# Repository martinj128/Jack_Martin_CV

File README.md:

# Jack_Martin_CV Repo

This repositry contains some personal projects I have invested my timein and also the complete work for my Final Year Dissertation which achieved publication in the CEAS Journal "SpaceWire in a Power Over Ethernet Environment".

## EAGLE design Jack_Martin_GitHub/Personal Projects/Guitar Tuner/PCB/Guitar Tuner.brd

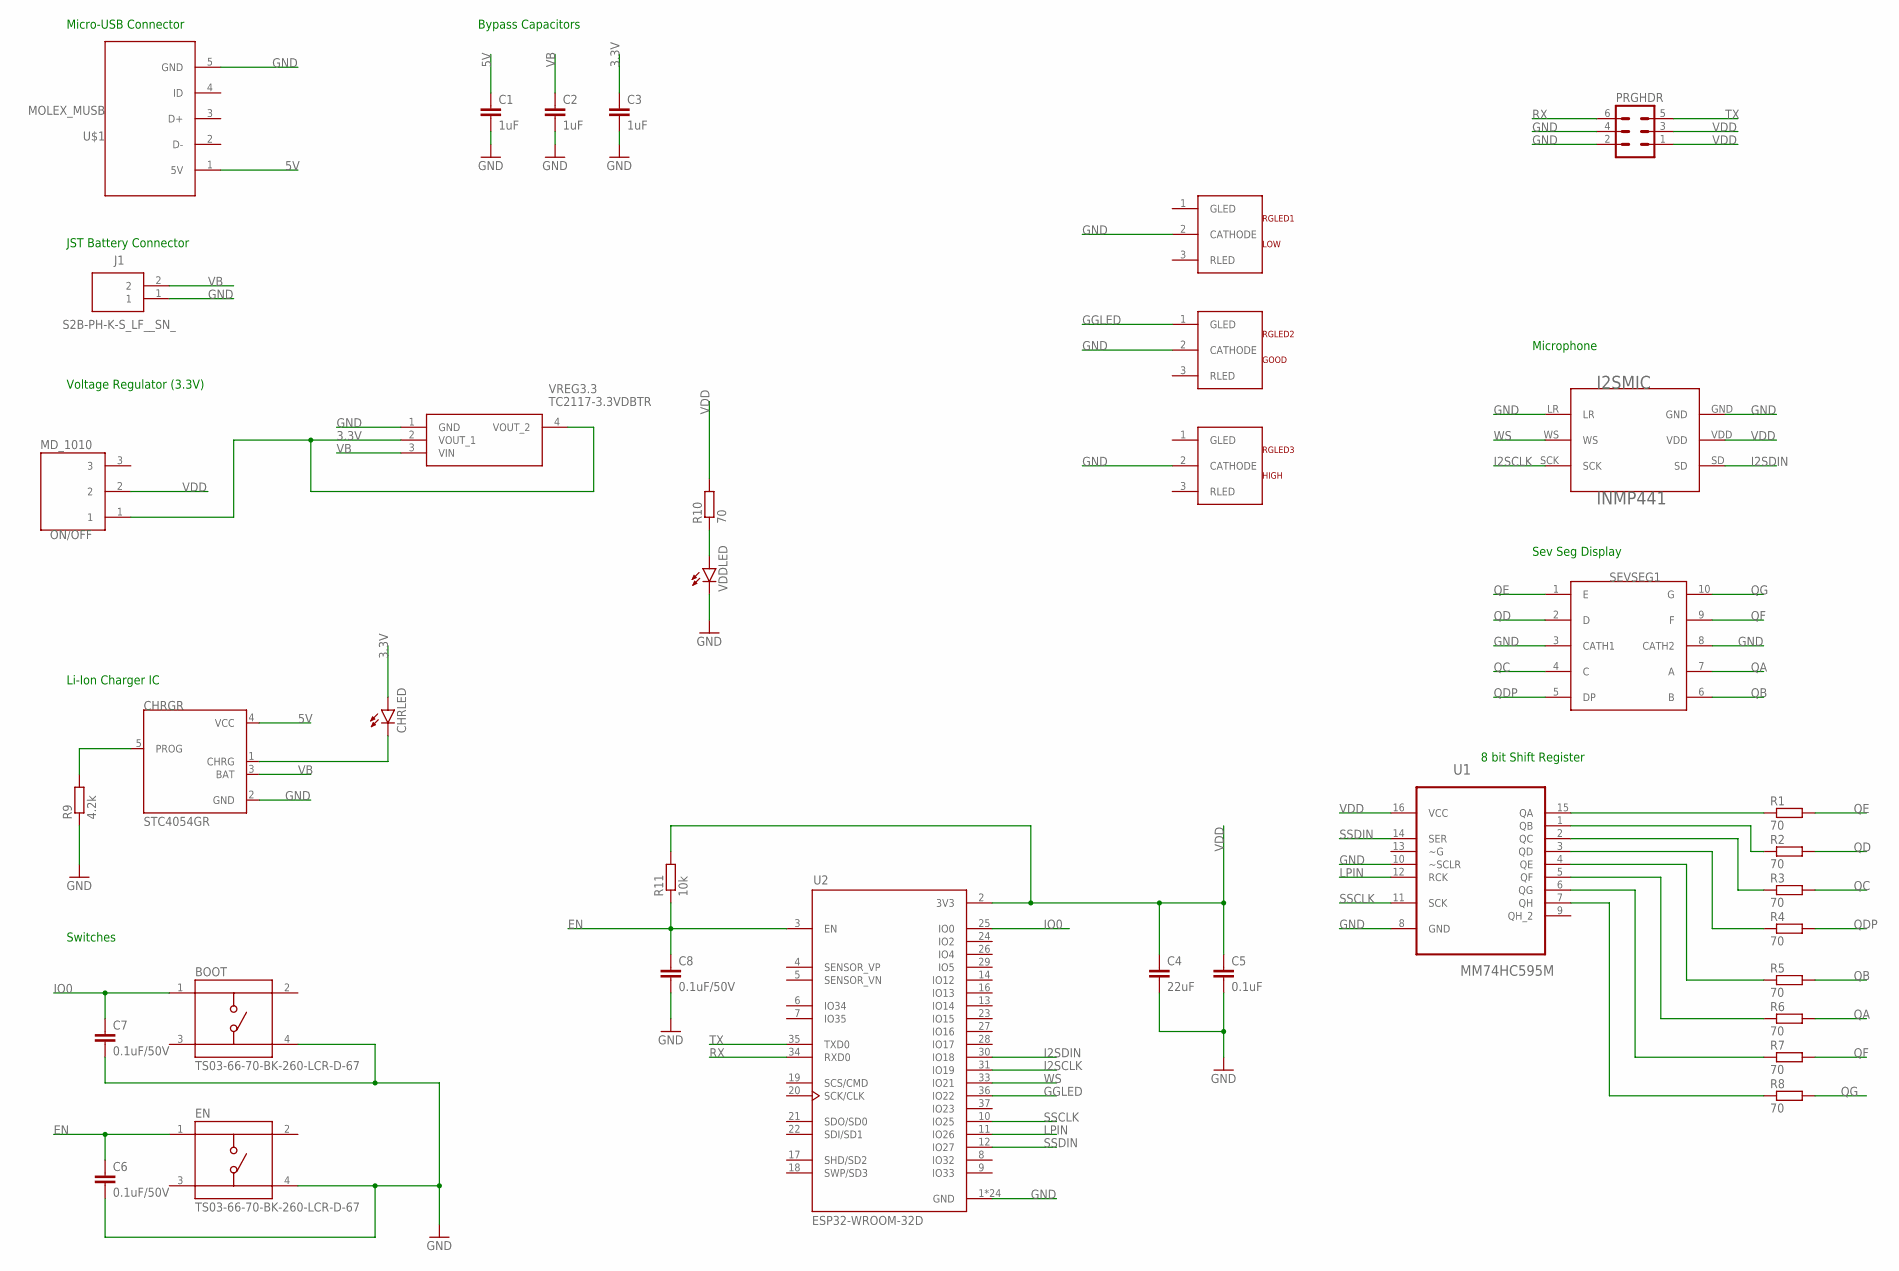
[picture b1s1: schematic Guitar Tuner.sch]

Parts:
BOOT: TS03-66-70-BK-260-LCR-D-67; SW_TS03-66-70-BK-260-LCR-D-67
C1, C2, C3: 1uF; C0805
C4: 22uF; C0805
C5: 0.1uF; C0805
C6, C7, C8: 0.1uF/50V; C0805
CHRGR: STC4054GR; SOT95P280X110-5N
CHRLED: LED5MM
EN: TS03-66-70-BK-260-LCR-D-67; SW_TS03-66-70-BK-260-LCR-D-67
I2SMIC: INMP441
J1: S2B-PH-K-S_LF__SN_; SHDRRA2W50P0X200_1X2_590X760X4
ON/OFF: MD_1010; MP_1010
PRGHDR: MA03-2
R1, R2, R3, R4, R5, R6, R7, R8, R10: 70; R0805
R9: 4.2k; R0805
R11: 10k; 0207/10
RGLED1: LOW; HLMP-0800
RGLED2: GOOD; HLMP-0800
RGLED3: HIGH; HLMP-0800
SEVSEG1: LS0803GWK
U1: MM74HC595M; SOIC127P600X175-16N
U2: ESP32-WROOM-32D; MODULE_ESP32-WROOM-32D
U$1: MOLEX_MUSB
VDDLED: LED5MM
VREG3.3: TC2117-3.3VDBTR; SOT230P700X180-4N

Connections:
3.3V: C3.1, CHRLED.A, ON/OFF.1, VREG3.3.2 (VOUT_1), VREG3.3.4 (VOUT_2)
5V: C1.1, CHRGR.4 (VCC), U$1.1 (5V)
EN: C6.1, C8.1, EN.1, R11.1, U2.3 (EN)
GGLED: RGLED2.1 (GLED), U2.36 (IO22)
GND: BOOT.4, C1.2, C2.2, C3.2, C4.2, C5.2, C6.2, C7.2, C8.2, CHRGR.2 (GND), EN.4, I2SMIC.GND, I2SMIC.LR, J1.1, PRGHDR.2, PRGHDR.4, R9.1, RGLED1.2 (CATHODE), RGLED2.2 (CATHODE), RGLED3.2 (CATHODE), SEVSEG1.3 (CATH1), SEVSEG1.8 (CATH2), U1.8 (GND), U1.10 (~SCLR), U2.1 (GND), U2.15 (GND), U2.38 (GND), U2.39_1 (GND), U2.39_2 (GND), U2.39_3 (GND), U2.39_4 (GND), U2.39_5 (GND), U2.39_6 (GND), U2.39_7 (GND), U2.39_8 (GND), U2.39_9 (GND), U2.39_10 (GND), U2.39_11 (GND), U2.39_12 (GND), U2.39_13 (GND), U2.39_14 (GND), U2.39_15 (GND), U2.39_16 (GND), U2.39_17 (GND), U2.39_18 (GND), U2.39_19 (GND), U2.39_20 (GND), U2.39_21 (GND), U$1.5 (GND), VDDLED.K (C), VREG3.3.1 (GND)
I2SCLK: I2SMIC.SCK, U2.31 (IO19)
I2SDIN: I2SMIC.SD, U2.30 (IO18)
IO0: BOOT.1, C7.1, U2.25 (IO0)
LPIN: U1.12 (RCK), U2.11 (IO26)
unnamed: R1.1, U1.15 (QA)
unnamed: R2.1, U1.1 (QB)
unnamed: R3.1, U1.2 (QC)
unnamed: R4.1, U1.3 (QD)
unnamed: R5.1, U1.4 (QE)
unnamed: R6.1, U1.5 (QF)
unnamed: R7.1, U1.6 (QG)
unnamed: R8.1, U1.7 (QH)
unnamed: CHRGR.5 (PROG), R9.2
unnamed: CHRGR.1 (CHRG), CHRLED.K (C)
unnamed: R10.1, VDDLED.A
QA: R6.2, SEVSEG1.7 (A)
QB: R5.2, SEVSEG1.6 (B)
QC: R3.2, SEVSEG1.4 (C)
QD: R2.2, SEVSEG1.2 (D)
QDP: R4.2, SEVSEG1.5 (DP)
QE: R1.2, SEVSEG1.1 (E)
QF: R7.2, SEVSEG1.9 (F)
QG: R8.2, SEVSEG1.10 (G)
RX: PRGHDR.6, U2.34 (RXD0)
SSCLK: U1.11 (SCK), U2.10 (IO25)
SSDIN: U1.14 (SER), U2.12 (IO27)
TX: PRGHDR.5, U2.35 (TXD0)
VB: C2.1, CHRGR.3 (BAT), J1.2, VREG3.3.3 (VIN)
VDD: C4.1, C5.1, I2SMIC.VDD, ON/OFF.2, PRGHDR.1, PRGHDR.3, R10.2, R11.2, U1.16 (VCC), U2.2 (3V3)
WS: I2SMIC.WS, U2.33 (IO21)

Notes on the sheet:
Bypass Capacitors
Micro-USB Connector
JST Battery Connector
Voltage Regulator (3.3V)
Li-Ion Charger IC
Switches
Microphone
Sev Seg Display
8 bit Shift Register

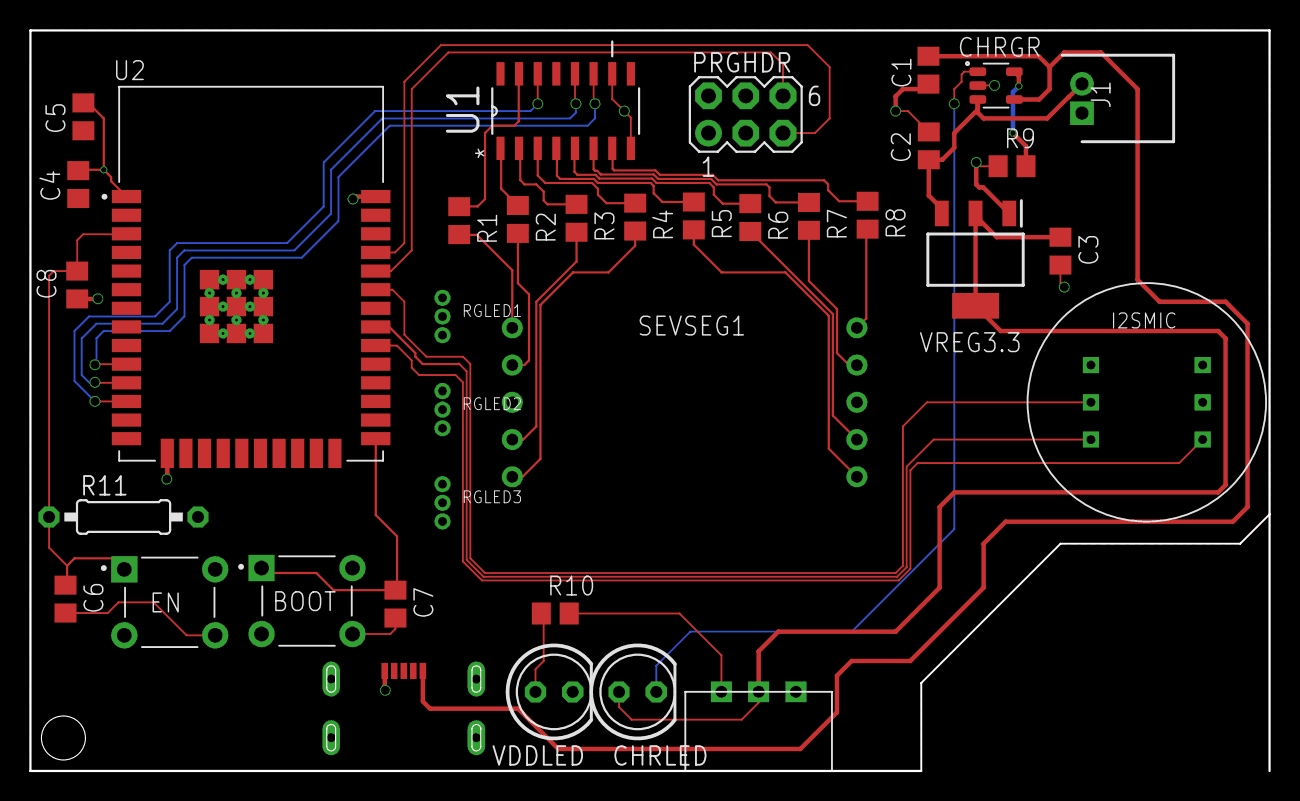
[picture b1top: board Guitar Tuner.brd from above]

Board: 2 copper layers, 84.5 x 50.5 mm, 36 parts (0 on the bottom side), 35 nets.
